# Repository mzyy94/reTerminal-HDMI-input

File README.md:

# reTerminal-HDMI-input

HDMI input expansion module for reTerminal

## Story

Read [reTerminalとHDMI入力でゲーム配信！ - HDMI入力拡張モジュール - \| ProtoPedia](https://protopedia.net/prototype/2933).

## Hardwares

- [H2C-RPI-B01](http://s.click.aliexpress.com/e/_dTNt3wP)
- [Button SHIM](https://shop.pimoroni.com/products/button-shim)
- M2.5 screw
- M4 screw

## Resources

This repository includes following resources:

- [Hardware patch for H2C-RPI-B01](patch)
- [dtoverlay for reTerminal](overlays)
- [3D printable enclosure model](case)
- [Demo application](app)

## License

Licensed under GPL v2. See [LICENSE](LICENSE)

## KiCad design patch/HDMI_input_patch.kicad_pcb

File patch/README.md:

# Hardware patch for cheap HDMI input board

_Originally from [[UPDATED, SOLVED] Why "cheap" Chinese HDMI-to-CSI2 adapters (e.g.18810-1 C779) don't provide I2S sound - Raspberry Pi Forums](https://forums.raspberrypi.com/viewtopic.php?p=1695619)_

Cheap HDMI board doesn't have APLL circuit. This patch adds it to the board.

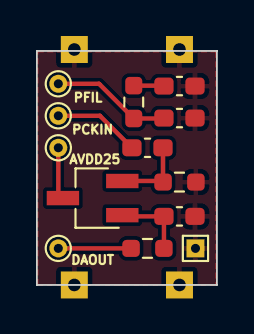
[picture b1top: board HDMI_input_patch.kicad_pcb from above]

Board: 2 copper layers, 10.0 x 13.0 mm, 8 parts (0 on the bottom side), 5 nets.

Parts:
C1, C5: 1000pF; C_0603_1608Metric_Pad1.08x0.95mm_HandSolder
C2: 0.1uF; C_0603_1608Metric_Pad1.08x0.95mm_HandSolder
C4: 5pF; C_0603_1608Metric_Pad1.08x0.95mm_HandSolder
Q1: 2SC2712Y; SC-59_Handsoldering
R1, R3: 1.0k; R_0603_1608Metric_Pad0.98x0.95mm_HandSolder
R2: 1.5k; R_0603_1608Metric_Pad0.98x0.95mm_HandSolder

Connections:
/PFIL: C1.1, R1.1
GND: C1.2, C2.2, C4.2, R3.2
unnamed: C2.1, R1.2
unnamed: C4.1, Q1.1 (B), R2.2
unnamed: C5.1, Q1.2 (E), R3.1

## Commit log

2022-02-14 Case model STL v1
2022-02-14 Case model STEP v1
2022-02-21 app: Create window
2022-02-21 app: Split activate function
2022-02-21 app: Add gstreamer videotestsrc widget
2022-02-21 app: Add video caps 1280x720
2022-02-21 app: Remove independent gdk
2022-02-21 app: Update layout
2022-02-25 Import tc358743-overlay.dts
    from https://github.com/raspberrypi/linux/blob/rpi-5.10.y/arch/arm/boot/dts/overlays/tc358743-overlay.dts
2022-02-25 Apply patch
    from https://forums.raspberrypi.com/viewtopic.php?t=303226
2022-02-25 Create build makefile
2022-02-26 Change license to GPLv2
2022-02-26 Add APLL patch circuit
2022-02-27 Update and create READMEs
2022-02-28 overlays: Add reference
2022-03-03 patch: Update PCB design
2022-03-03 patch: Add KiCad project
2022-03-05 app: Add fullscreen option
2022-03-05 app: Set background color
2022-03-05 app: Add video preview area
2022-03-05 app: Add layout explain
2022-03-05 app: Add icons from https://google.github.io/material-design-icons/
2022-03-05 app: Add action buttons
2022-03-05 app: Create action mod
2022-03-05 app: Add Roboto font from https://fonts.google.com/specimen/Roboto
2022-03-05 app: Add bottom actions
2022-03-05 app: Change to solid style
2022-03-05 app: Add settings button
2022-03-06 app: Create color bar image
2022-03-06 app: Show color bar image in preview area
2022-03-06 app: Change icon images to icon font
2022-03-06 app: Add Message type of enum
2022-03-07 app: Improve layout
2022-03-07 app: Add video source feature flag
2022-03-07 app: Create level meter
2022-03-07 app: Add debug feature flag
2022-03-07 app: Remove colorbar image
2022-03-07 app: Add RobotoMono font
2022-03-07 app: Add status area mock
2022-03-07 app: Create gstreamer pipeline
2022-03-07 app: Add keyboard event
2022-03-07 app: Fix button color
2022-03-07 app: Convert video format using opengl
2022-03-07 app: Add font module
2022-03-07 app: Update iced which support Vulkan on Raspberry Pi 4
2022-03-07 app: Create Stream struct
2022-03-07 app: Rename module pipeline to stream
2022-03-07 app: Create audio pipeline
2022-03-07 app: Use single_value_channel instead of mpsc
2022-03-07 app: Make better level meter
2022-03-08 app: Create element! macro
2022-03-08 app: Improve frame update event
2022-03-08 app: Change rms calc method from appsink to level element
2022-03-08 app: Add right channel level meter
2022-03-10 app: Change level update interval to 30ms
2022-03-10 app: Improve frame and level field access
2022-03-10 app: Create widget module
2022-03-10 app: Add glvideomixer element
2022-03-10 app: Shorten buffer control code
2022-03-10 app: Create camera toggle button action
2022-03-10 app: Add actionable camera button
2022-03-10 app: Create rtmp streaming function
2022-03-11 app: Create element module
2022-03-11 app: Apply rustfmt with 4 spaces indent
2022-03-11 app: Split control view as module
2022-03-11 app: Add setting view module
2022-03-11 app: Use streaming url in setting
2022-03-11 app: Replace stream key in template url
2022-03-11 app: Display rtmp host name
2022-03-11 app: Create twitch ingest list
2022-03-12 app: Show streaming duration
2022-03-12 app: Fix missing stream key
2022-03-12 app: Add mic toggle function
2022-03-12 app: Change encoder
2022-03-12 app: Add device configuration env-var
2022-03-13 app: Remove too much fields of caps
2022-03-13 app: Add missing queue elements after tee
2022-03-13 app: Replace fonts
2022-03-13 app: Use global setting
2022-03-13 app: Remove config crate
2022-03-13 app: Reduce read blocking
2022-03-13 app: Add ViewApp trait
2022-03-13 app: Move View enum
2022-03-13 app: Add local scoped Message enum in view
2022-03-13 app: Remove ingest selection view
2022-03-13 app: Use dynamic ingest server on start streaming
2022-03-13 app: Add saving method of setting
2022-03-13 app: Add nested setting sections
2022-03-13 app: Load setting file on start up
2022-03-15 app: Add button shim LED status indicator
2022-03-16 app: Add mic level meter
2022-03-16 app: Fix link/unlink order
2022-03-16 app: Add mic level value
2022-03-16 app: Add meter limit
2022-03-16 app: Add microphone mode setting
2022-03-16 app: Create label widget
2022-03-16 app: Add side button actions
2022-03-16 app: Remove ping meter
2022-03-16 app: Add cpu usage
2022-03-17 app: Improve encoding performance
2022-03-17 app: Create README.md
2022-03-17 Add app resource link
2022-03-17 Add app screenshot
